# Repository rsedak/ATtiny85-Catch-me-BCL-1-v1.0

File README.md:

[Croatian version](README_HR-HR.md).

Introduction
============
My friend Zvonimir Lapov asked me if I could design THT PCB which would be used in primary school student education.
Purpose of 'Catch me BCL-1' module is student education. It shows advantages of charlieplexing with seven BI-color LEDs.
This version is designed for the case when the BI-color LED has a brighter LED on pin 1.
There are many variations of bi-color LEDs on the market, so you will need to define the resistors yourself.

Photo by Robert Sedak

Warning:
------------
In order for the program to be fully executed, the RESET pin on the ATtiny must be declared as an input/output pin. This is achieved by activating the FUSE bit called RSTDISBL. If we want to reprogram the ATtiny afterwards, we must turn off the FUSE bit called RSTDISBL using the high-voltage (12V) programming technique.
The procedure for programming the FUSE bits and the high-voltage programming technique can be found in professional literature. Use your newly acquired knowledge only when you fully understand what you have to do. Otherwise, you may damage the microcontroller.

Contributor
------------
- Robert Sedak — features, programming, schematic design, CAD design, case for PCB
- Zvonimir Lapov - idea

Application
-----------
Robert Sedak made a video with example programmed in Arduino IDE with ATtiny85 support:

Photo by Robert Sedak

You can download example for Arduino IDE from [here](examples/).

Bill Of Materials
-----------------
- 1 ea., PCB
- 5 ea., 100 ohm 1/4W 1% Resistor (R1, R2, R3, R4, R5)
- 7 ea., 1K ohm 1/4W 1% Resistor (R6, R7, R8, R9, R10, R11, R12)
- 7 ea., BI-color LED 5mm (D1, D2, D3, D4, D5, D6, D7) with common cathode
- 4 ea., 6x6x4.3mm SPST Momentary push switch (SW1)
- 1 ea., SDPT 1P2T slide switch (SW2)
- 1 ea., 100nF 50V Monolithic Ceramic Capacitor
- 1 ea., 8-Pin DIL IC Socket
- 1 ea., ATtiny85 or ATtiny13A
- 1 ea., battery holder Keystone 1060
- 1 ea., battery 2032

Design Files
------------
This project is designed using Open Source [KiCad](https://www.kicad.org/). Design files are located in the [design_files](design_files/) folder.  You can see the [schematic](images/attiny85_catch_me_bcl-1_schematic.pdf).

Gerber files
------------
You can download gerber files from [here](gerber/attiny85_catch_me_bcl-1.zip).

Firmware
--------
This project can be programmed using the Open Source [Arduino](https://www.arduino.cc/).
[ATTinyCore by Spence Konde](https://github.com/SpenceKonde/ATTinyCore) was used to program ATtiny85 in Arduino IDE
[MicroCore by MCUdude](https://github.com/MCUdude/MicroCore) was used to program ATtiny13 in Arduino IDE.
Arduino examples for Arduino IDE are located in [examples](examples/) folder.

Case
-------
Robert Sedak created case for PCB. You can download STL and FCStd file from [case](case/) folder.
This case was designed using Open Spource [FreeCAD](https://www.freecad.org/).

**Bill Of Connecting Materials**
- 4 ea., M3 nuts
- 4 ea., M3x5mm + 4mm  Male to Female plastic Hex Spacer
- 4 ea., M3x5mm plastic screw

Photo by Robert Sedak

Photo by Robert Sedak

License
-------
[Attribution-ShareAlike 4.0 International (CC BY-SA 4.0)](https://creativecommons.org/licenses/by-sa/4.0/)

You are free to:
- Share — copy and redistribute the material in any medium or format
- Adapt — remix, transform, and build upon the material

This license is acceptable for Free Cultural Works.
- The licensor cannot revoke these freedoms as long as you follow the license terms.

Under the following terms:
- Attribution — You must give appropriate credit, provide a link to the license, and indicate if changes were made. You may do so in any reasonable manner, but not in any way that suggests the licensor endorses you or your use.
- ShareAlike — If you remix, transform, or build upon the material, you must distribute your contributions under the same license as the original.

No additional restrictions — You may not apply legal terms or technological measures that legally restrict others from doing anything the license permits.

Reference Designs ARE PROVIDED "AS IS" AND "WITH ALL FAULTS". Authors DISCLAIMS ALL OTHER WARRANTIES, EXPRESS OR IMPLIED, REGARDING PRODUCTS, INCLUDING BUT NOT LIMITED TO, ANY IMPLIED WARRANTIES OF MERCHANTABILITY OR FITNESS FOR A PARTICULAR PURPOSE.
Authors may make changes to specifications and product descriptions at any time, without notice. The Customer must notrely on the absence or characteristics of any features or instructions marked "reserved" or "undefined."
Authors reservesthese for future definition and shall have no responsibility whatsoever for conflicts or incompatibilities arising from future changes to them. The product information on the Web Site or Materials is subject to change without notice. Do not finalize a design with this info.

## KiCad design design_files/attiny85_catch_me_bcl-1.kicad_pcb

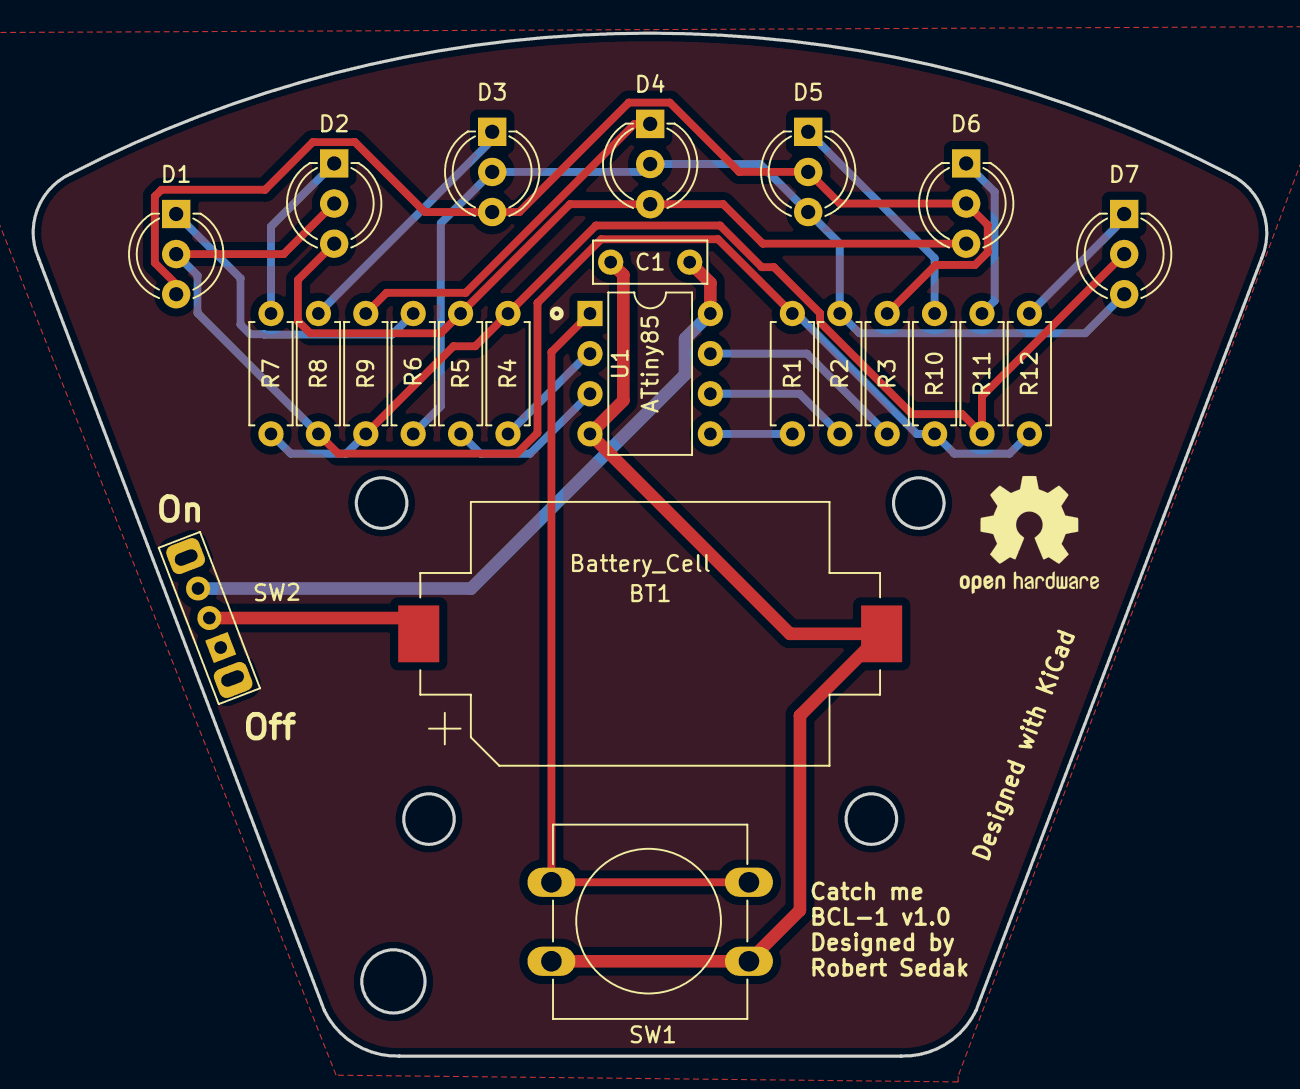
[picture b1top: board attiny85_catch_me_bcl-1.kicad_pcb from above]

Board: 2 copper layers, 78.1 x 64.7 mm, 24 parts (0 on the bottom side), 21 nets.

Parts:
BT1: Battery_Cell; BatteryHolder_Keystone_1060_1x2032
C1: 0.1uF; C_Rect_L7.0mm_W2.5mm_P5.00mm
D1, D2, D3, D4, D5, D6, D7: LED_Dual_AKA; LED_D5.0mm-3
R1, R2, R3, R4, R5, R6, R7, R8, R9, R10, R11, R12: 120R; R_Axial_DIN0207_L6.3mm_D2.5mm_P7.62mm_Horizontal
SW1: SW_Push; SW_PUSH-12mm
SW2: SW_Push_SPDT; SW_Slide_SPDT_1P2TC_right_angle
U1: ATtiny85; DIP-8_W7.62mm

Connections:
unnamed: BT1.1 (+), SW2.2 (B)
unnamed: BT1.2 (-), C1.2, SW1.1, U1.4 (GND)
unnamed: C1.1, SW2.3 (C), U1.8 (VCC)
unnamed: D1.1 (A1), R6.1
unnamed: D2.1 (A1), R7.1
unnamed: D3.1 (A1), R8.1
unnamed: D4.1 (A1), R9.1
unnamed: D5.1 (A1), R10.1
unnamed: D6.1 (A1), R11.1
unnamed: D7.1 (A1), R12.1
unnamed: SW1.2, U1.1 (~RESET/PB5)
PB0: R1.1, U1.5 (AREF/PB0)
PB0R: D1.2 (K), D2.2 (K), R1.2, R8.2, R10.2, R12.2
PB1: R2.1, U1.6 (PB1)
PB1R: D3.2 (K), D4.2 (K), D5.3 (A2), D7.3 (A2), R2.2, R6.2
PB2: R3.1, U1.7 (PB2)
PB2R: D1.3 (A2), D3.3 (A2), D5.2 (K), D6.2 (K), R3.2
PB3: R4.1, U1.2 (XTAL1/PB3)
PB3R: D7.2 (K), R4.2, R7.2, R9.2, R11.2
PB4: R5.1, U1.3 (XTAL2/PB4)
PB4R: D2.3 (A2), D4.3 (A2), D6.3 (A2), R5.2

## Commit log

2026-01-11 link change
2026-01-11 minor change

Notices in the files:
design_files/attiny85_catch_me_bcl-1.kicad_pcb:
License: CC-BY-SA 4.0
